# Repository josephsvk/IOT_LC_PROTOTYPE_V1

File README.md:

# IOT_LC_PROTOTYPE_V1

## Requirements typically met:

	- USB Pair > 92.51 ohm Zd
	- AC insulation using 2 mm cutouts in the board; the rest is 3 mm , OVC III, PD2
	- Option to install two different 24V power sources
	- Properly designed GND boards and VIAS , zone minimum width 0.3 mm
	- The area under the antenna connector has been cleaned
	-

Modular IoT controller — custom PCB hardware project designed in KiCad 10.

**Status:** Work in progress — prototype, not validated for production.

This repository contains the KiCad schematic, PCB layout, design rules, and generated technical documentation.

> **Safety:** The design includes mains-voltage circuitry. It has not been certified or validated for safe mains operation. Do not assume that the published design is safe to manufacture or energize.

## Project Files

- `IOT_LC_PROTOTYPE_V1.kicad_pro` — KiCad project configuration
- `IOT_LC_PROTOTYPE_V1.kicad_sch` — Main schematic
- `IOT_LC_PROTOTYPE_V1.kicad_pcb` — PCB layout
- `IOT_LC_PROTOTYPE_V1.kicad_dru` — Custom design rules
- `*.kicad_sch` — Hierarchical schematic sheets

## Automation Scripts

### `scripts/export-pdf.sh`

Generates vector PDF documentation and PNG previews for this README.

```bash
./scripts/export-pdf.sh
```

Requirements: KiCad CLI 10 and `poppler-utils`.

### `scripts/auto-git.sh`

Automatically commits saved project changes and pushes them to GitHub.

- Runs through a local systemd user timer.
- Checks for changes approximately every 15 minutes.
- Respects `.gitignore`.
- Creates commits only when changes exist.
- Does not use force push.

The timer is configured locally and is not installed automatically when cloning this repository.

## Documentation

PDF and PNG files in `docs/` are generated from the KiCad source files.

The README displays PNG previews. The linked PDF files provide vector-quality documentation.

## License

No license has been specified. All rights reserved unless a license is added.

<!-- AUTO-DOCS-START -->
## Schematic documentation

### Complete active hierarchical schematic

**Page 1**

**Page 2**

**Page 3**

[View vector PDF](docs/pdf/schematic.pdf)

## PCB documentation

### PCB front

**Page 1**

[View vector PDF](docs/pdf/pcb-front.pdf)

### PCB back

**Page 1**

[View vector PDF](docs/pdf/pcb-back.pdf)

### Individual PCB layers

**Page 1**

**Page 2**

**Page 3**

**Page 4**

[View vector PDF](docs/pdf/pcb-layers.pdf)
<!-- AUTO-DOCS-END -->

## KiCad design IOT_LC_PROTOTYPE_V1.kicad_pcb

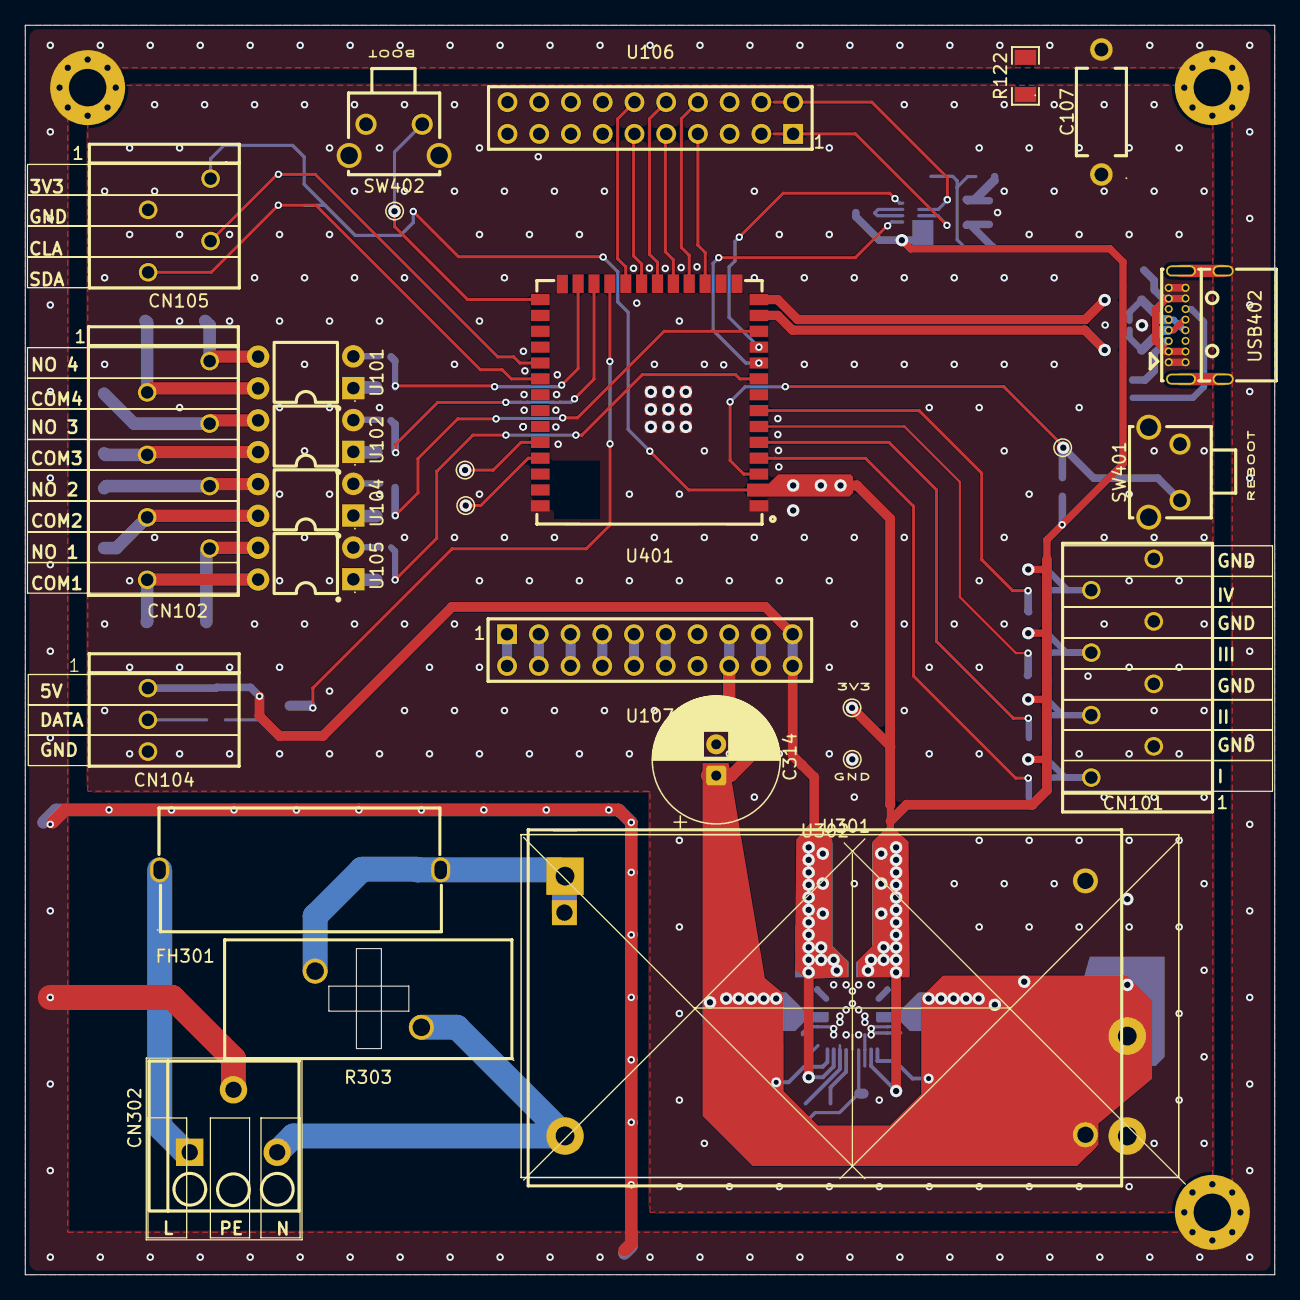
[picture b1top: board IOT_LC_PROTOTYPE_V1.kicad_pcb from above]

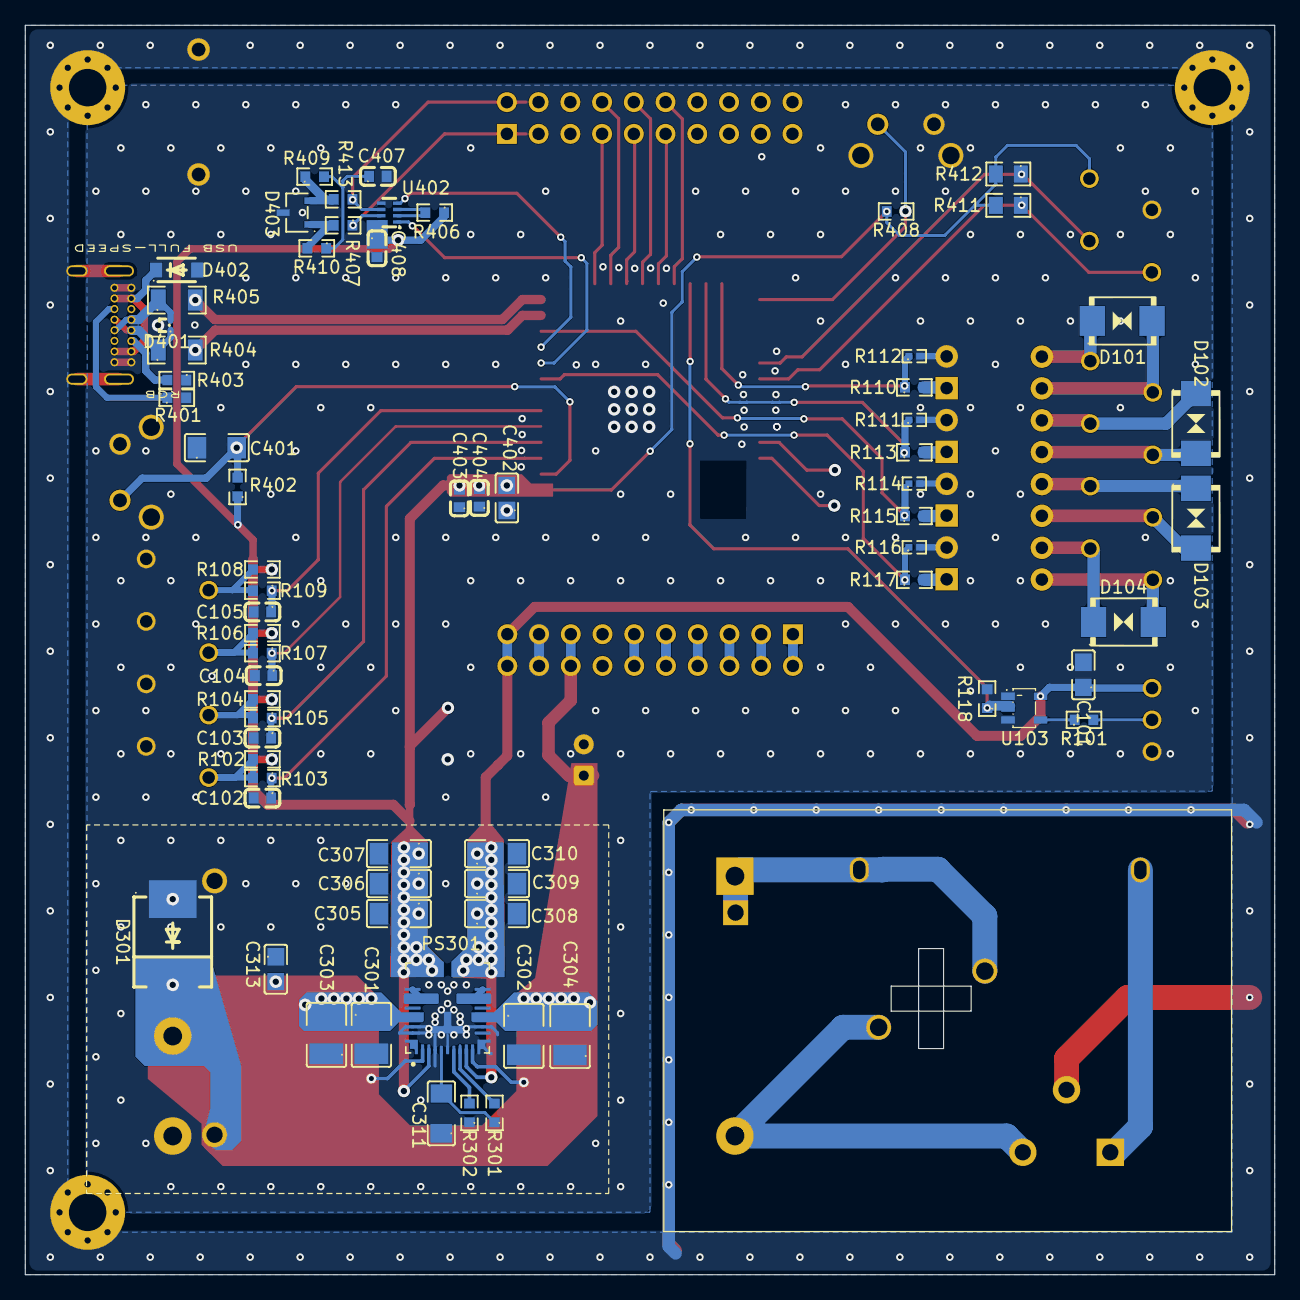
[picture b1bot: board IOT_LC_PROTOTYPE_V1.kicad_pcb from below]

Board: 2 copper layers, 100.0 x 100.0 mm, 98 parts (67 on the bottom side), 73 nets.

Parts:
C101: C0805C104K5RACTU_C3018562; C0805
C102, C103, C104, C105: C0603C103K5RACTU; C0603
C107: DE1E3RA102MA4BN01F; CAP-TH_L7.0-W4.0-P10.00-D0.6
C301, C302, C303, C304: 12105C106KAT2A; C1210
C305, C308, C311: CC1206KKX7R8BB105; C1206
C306, C307, C309, C310: GRM31CR71H225KA88L; C1206
C313: CC0805JKX7R9BB105; C0805
C314: NRSZ101M50V10X12.5F; CP_Radial_D10.0mm_P2.50mm
C401: C1206C105K5RACTU; C1206
C402: C2012X7R1A106K125AC; C0805
C403: FCC0603B105K160CT; C0603
C404, C408: C0603C104K4RACTU; C0603
C407: CC0603KRX7R9BB472; C0603
CN101, CN102: 1990067; CONN-TH_8P-P2.50_1990067
CN104: 1989751; CONN-TH_3P-P2.50_1989751
CN105: 1990025; CONN-TH_4P-P2.50_1990025
CN302: 1985205; CONN-TH_3P-P3.50_PHOENIX-CONTACT_1985205
D101, D102, D103, D104: SMBJ26CA_C83332; SMB_L4.6-W3.6-LS5.3-BI
D301: SMCJ26A-TR; SMC_L7.1-W6.2-LS8.1-RD
D401: TPD2EUSB30ADRTR; SOT-9X3-3_L1.0-W0.8-P0.35-LS1.0-BR
D402: SMF5.0A_C151296; SOD-123F_L2.8-W1.8-LS3.7-RD
D403: SM712.TCT; SOT-23-3_L3.0-W1.7-P0.95-LS2.9-BR
FH301: 65600001009; FUSE-TH_65600001009
H301, H303, H304: MountingHole_Pad; MountingHole_3mm_Pad_Via
PS301: TLVM14406RCHR; CONV_TLVM14406RCHR
R101, R110, R113, R115, R117: ERJ3EKF3300V; R0603
R102, R104, R106, R108: ERJPA3F4701V; R0603
R103, R105, R107, R109: ERJ-3EKF1001V; R0603
R111, R112, R114, R116: ERJ2RKF4702X; R0402
R118, R402, R406, R408: ERA-3AEB103V; R0603
R122: CRCW12061M00FKEA; R1206
R301: ERJ-3EKF1002V; R0603
R302: ERJ3EKF1542V; R0603
R303: TMOV20RP275E; RES-TH_L23.0-W9.5-P8.50-D0.9-S4.50
R401, R403: RC0603FR-075K1L; R0603
R404, R405: CRCW120622R0FKEA; R1206
R407, R413: ERJ-3GEY0R00V; R0603
R409, R410: CRCW060360R4FKEA; R0603
R411, R412: AC0805FR-7W2K2L; R0805
SW401, SW402: 1825027-5; KEY-TH_4P-L7.5-W6.8-P4.50-LS7.2
TP401, TP402, TP403, TP404, TP405, TP406: TestPoint; TestPoint_Pad_D1.0mm
U101, U102, U104, U105: AQY211EH; DIP-4_L6.4-W4.8-P2.54-LS7.6-BL
U103: SN74AHCT1G125DBVR; SOT-23-5_L3.0-W1.7-P0.95-LS2.8-BR
U106, U107: SSQ-110-02-T-D; HDR-TH_ESQ-110-23-G-D
U301: IRM-20-24; Converter_ACDC_MeanWell_IRM-20-xx_THT
U302: HLK-15M24C; PWRM-TH_4P-L47.5-W28.5_HLK-15MXXC
U401: ESP32-S3-WROOM-1U-N16R8; WIRELM-SMD_ESP32-S3-WROOM-1U
U402: THVD1426DRLR_C5215922; SOT-583-8_L2.1-W1.2-P0.50-LS1.6-BR
USB402: USB4085-GF-A_C7095263; USC-C-SMD_USB4085-GF-A

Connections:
5V: U107.3, U107.4
5V_BATT: U107.9, U107.10
5V_LOGIC: C101.1, C308.1, C309.1, C310.1, CN104.1, PS301.9 (COMP/VOSNS2), PS301.18 (VOUT/VOUT2), PS301.19 (VOUT/VOUT2), U103.5 (VCC), U107.19, U107.20
24V: U107.1, U107.2
24V_BATT: U107.7, U107.8
24V_LOGIC: C301.1, C302.1, C303.2, C304.2, C313.2, C314.1, D301.1, PS301.2 (EN1), PS301.10 (EN2), PS301.14 (VIN2), PS301.25 (VIN1), U107.15, U107.16, U301.4 (+Vo), U302.4 (+VO)
/36V_TO_5V+3V3/AC_L_FUSE_LINE: FH301.2, R303.2, U301.1 (AC/L), U302.1 (AC)
/36V_TO_5V+3V3/AC_L_LINE: CN302.1, FH301.1
/36V_TO_5V+3V3/AC_N_LINE: CN302.3, R303.1, U301.2 (AC/N), U302.2 (AC)
/36V_TO_5V+3V3/VCC: C311.2, PS301.5 (VCC), R301.1
/DIGITUS_ANULARIS: C105.1, R109.1, U401.7 (IO7)
/DIGITUS_MEDIUS: C104.1, R107.1, U401.6 (IO6)
/ESP32-S3-WROOM-1U-N16R8/ESP_BOOT: R408.1, SW402.1, TP406.1 (1_1), U401.27 (IO0)
/ESP32-S3-WROOM-1U-N16R8/ESP_EN: C401.2, R402.2, SW401.1, TP403.1 (1_1), U401.3 (EN)
/ESP32-S3-WROOM-1U-N16R8/UART_RX: U401.10 (IO17), U402.1 (R)
/ESP32-S3-WROOM-1U-N16R8/UART_TX: U401.11 (IO18), U402.4 (D)
/ESP32-S3-WROOM-1U-N16R8/USB_CONN_N: D401.2 (D-), R405.1, USB402.A7 (Dn1), USB402.B7 (Dn2)
/ESP32-S3-WROOM-1U-N16R8/USB_CONN_P: D401.1 (D+), R404.1, USB402.A6 (Dp1), USB402.B6 (Dp2)
/ESP32-S3-WROOM-1U-N16R8/USB_N: R405.2, U401.14 (IO20)
/ESP32-S3-WROOM-1U-N16R8/USB_P: R404.2, U401.13 (IO19)
/ESP32-S3-WROOM-1U-N16R8/USB_VBUS: D402.1, USB402.A4 (VBUS), USB402.A9 (VBUS), USB402.B4 (VBUS), USB402.B9 (VBUS)
/INDEX: C102.1, R103.1, U401.4 (IO4)
/OS_Capitatum: R114.1, R115.1, U401.12 (IO8)
/OS_Hamatum: R116.1, R117.1, U401.9 (IO16)
/OS_Trapenzium: R110.1, R112.1, U401.25 (IO48)
/OS_Trapezoideum: R111.1, R113.1, U401.24 (IO47)
/POLLEX: C103.1, R105.1, U401.5 (IO5)
/RGB_DATA: R118.1, U103.2 (A), U401.23 (IO21)
BATT_GND: U107.11, U107.12
CHASSIS_GND: C107.2, CN302.2, H301.1 (1_1), H303.1 (1_1), H304.1 (1_1), R122.2, USB402.S1
GND: U107.5, U107.6
I2C_SCL: CN105.3, R412.1, U401.31 (IO38)
I2C_SDA: CN105.4, R411.1, U401.32 (IO39)
LOGIC_3V3: C305.1, C306.1, C307.1, C402.2, C403.2, C404.2, C408.1, CN105.1, PS301.3 (BIAS_VOSNS1), PS301.20 (VOUT/VOUT1), PS301.21 (VOUT/VOUT1), R102.1, R104.1, R106.1, R108.1, R402.1, R406.1, R408.2, R411.2, R412.2, TP401.1 (1_1), U401.2 (3V3), U402.8 (VCC)
LOGIC_GND: C101.2, C102.2, C103.2, C104.2, C105.2, C107.1, C301.2, C302.2, C303.1, C304.1, C305.2, C306.2, C307.2, C308.2, C309.2, C310.2, C311.1, C313.1, C314.2, C401.1, C402.1, C403.1, C404.1, C407.2, C408.2, CN101.2, CN101.4, CN101.6, CN101.8, CN104.3, CN105.2, D301.2, D401.3 (GND), D402.2, D403.3 (K), PS301.4 (FB1), PS301.6 (AGND), PS301.11 (CONFIG), PS301.13 (PGND), PS301.26 (PGND), PS301.27 (GND), PS301.28 (PGND), R111.2, R112.2, R114.2, R116.2, R118.2, R122.1, R302.1, R401.2, R403.1, SW401.2, SW401.3 (MH1), SW401.4 (MH2), SW402.2, SW402.3 (MH1), SW402.4 (MH2), TP402.1 (1_1), U101.2, U102.2, U103.1 (~OE), U103.3 (GND), U104.2, U105.2, U107.17, U107.18, U301.3 (-Vo), U302.3 (-VO), U401.1 (GND), U401.40 (GND), U401.41 (GND), U402.5 (GND), USB402.A1 (GND), USB402.A12 (GND), USB402.B1 (GND), USB402.B12 (GND)
unnamed: C407.1, R409.2, R410.1
unnamed: CN101.1, R102.2, R103.2
unnamed: CN101.3, R104.2, R105.2
unnamed: CN101.5, R106.2, R107.2
unnamed: CN101.7, R108.2, R109.2
unnamed: CN104.2, R101.2
unnamed: CN102.2, D101.2 (A), U101.4
unnamed: CN102.1, D101.1 (K), U101.3
unnamed: CN102.4, D102.2 (A), U102.4
unnamed: CN102.3, D102.1 (K), U102.3
unnamed: CN102.6, D103.2 (A), U104.4
unnamed: CN102.5, D103.1 (K), U104.3
unnamed: CN102.8, D104.2 (A), U105.4
unnamed: CN102.7, D104.1 (K), U105.3
unnamed: PS301.7 (RT), R302.2
unnamed: PS301.8 (SS/FB2), R301.2
unnamed: PS301.22 (SW1), PS301.23 (SW1)
unnamed: PS301.16 (SW2), PS301.17 (SW2)
unnamed: R110.2, U101.1
unnamed: R113.2, U102.1
unnamed: R115.2, U104.1
unnamed: R117.2, U105.1
unnamed: R101.1, U103.4 (Y)
unnamed: R413.1, U402.6 (A)
unnamed: R407.1, U402.7 (B)
unnamed: R406.2, U402.2 (~RE), U402.3 (~SHDN)
unnamed: R403.2, USB402.A5 (CC1)
unnamed: R401.1, USB402.B5 (CC2)
RS485_A: D403.2 (A1), R409.1, R413.2, U106.2
RS485_B: D403.1 (A1), R407.2, R410.2, U106.1
SPI_CS2: U106.7, U401.17 (IO9)
SPI_DC: U106.12, U401.22 (IO14)
SPI_MISO: U106.11, U401.21 (IO13)
SPI_MOSI: U106.9, U401.19 (IO11)
SPI_SC1: U106.8, U401.18 (IO10)
SPI_SCK: U106.10, U401.20 (IO12)
UART_RX: TP405.1 (1_1), U401.36 (RXD0)
UART_TX: TP404.1 (1_1), U401.37 (TXD0)
